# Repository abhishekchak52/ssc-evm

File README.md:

# ssc-evm
The Electronic Voting Machine for the St. Stephen's College Student's Union Society Elections for 2016-2017. With love from the Electronics Society

The basic design of the EVM is based on the Atmel ATmega328 chip which is at the heart of the Arduino UNO.
The final circuit will use only the chip instead of the entire Arduino board. The code is written in the Arduino language.

##TODO
* Make a working prototype using the Arduino UNO.
* Test for bugs.
* Port to a 40 AVR PDIP chip.

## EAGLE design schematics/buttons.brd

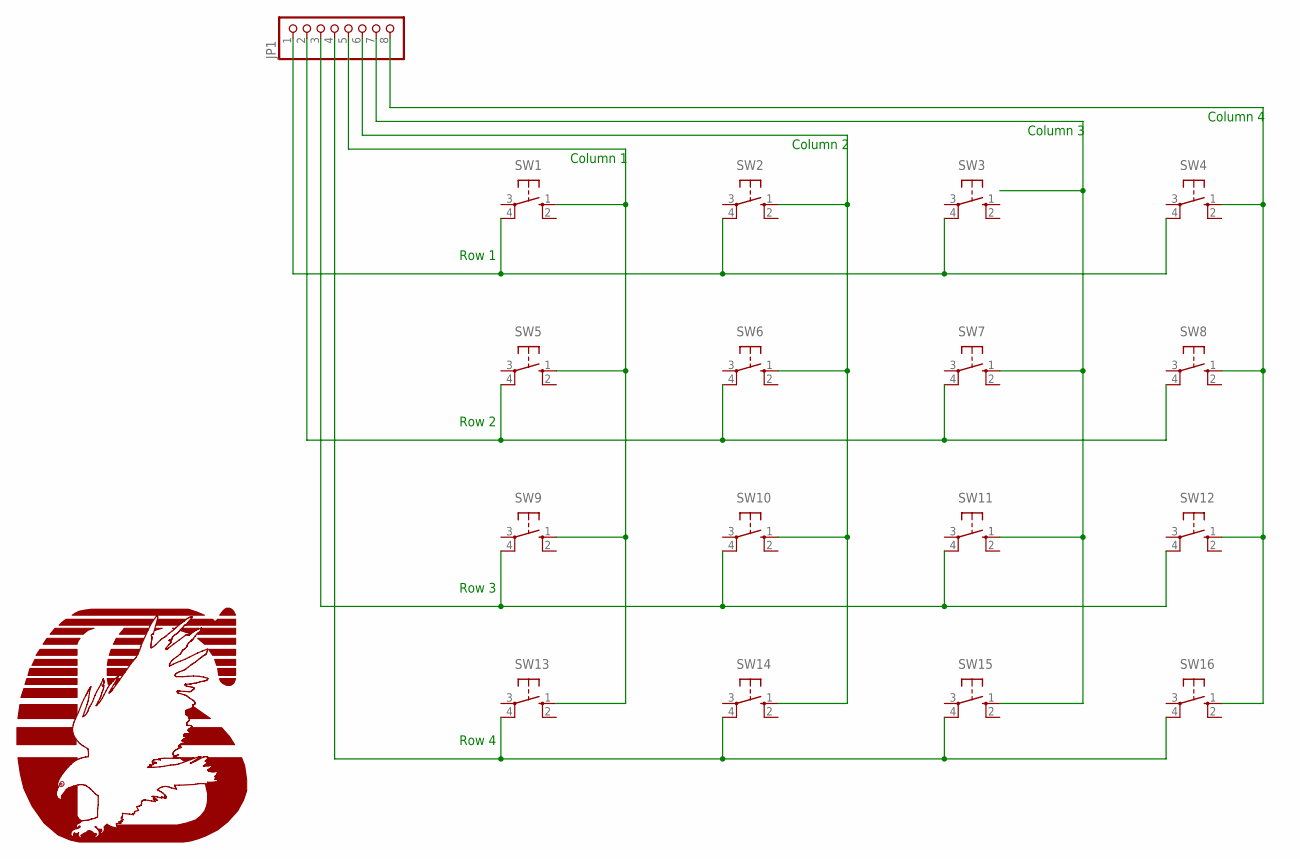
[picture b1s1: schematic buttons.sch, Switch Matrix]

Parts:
JP1: PINHD-1X8-3.5MM; 1X08-3.5MM
SW1, SW2, SW3, SW4, SW5, SW6, SW7, SW8, SW9, SW10, SW11, SW12, SW13, SW14, SW15, SW16: 10-XX; B3F-10XX

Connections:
unnamed: JP1.1, SW1.4 (P1), SW2.4 (P1), SW3.4 (P1), SW4.4 (P1)
unnamed: JP1.2, SW5.4 (P1), SW6.4 (P1), SW7.4 (P1), SW8.4 (P1)
unnamed: JP1.3, SW9.4 (P1), SW10.4 (P1), SW11.4 (P1), SW12.4 (P1)
unnamed: JP1.4, SW13.4 (P1), SW14.4 (P1), SW15.4 (P1), SW16.4 (P1)
unnamed: JP1.5, SW1.1 (S), SW5.1 (S), SW9.1 (S), SW13.1 (S)
unnamed: JP1.6, SW2.1 (S), SW6.1 (S), SW10.1 (S), SW14.1 (S)
unnamed: JP1.7, SW7.1 (S), SW11.1 (S), SW15.1 (S)
unnamed: JP1.8, SW4.1 (S), SW8.1 (S), SW12.1 (S), SW16.1 (S)

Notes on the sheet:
Row 1
Row 2
Row 3
Row 4
Column 1
Column 2
Column 3
Column 4

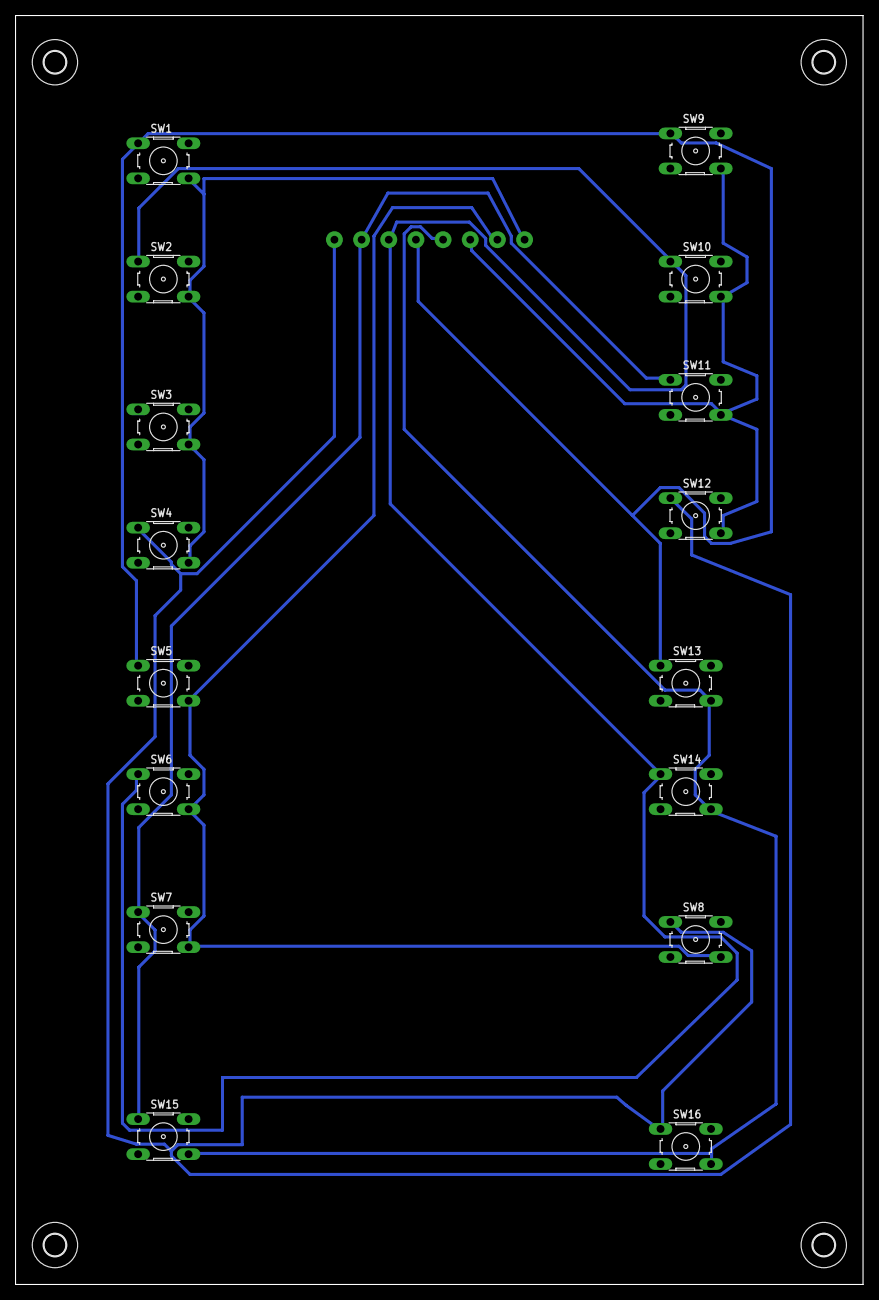
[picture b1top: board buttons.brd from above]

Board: 2 copper layers, 109.2 x 163.5 mm, 21 parts (1 on the bottom side), 8 nets.

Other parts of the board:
U$1, U$2, U$3, U$4: 2,8

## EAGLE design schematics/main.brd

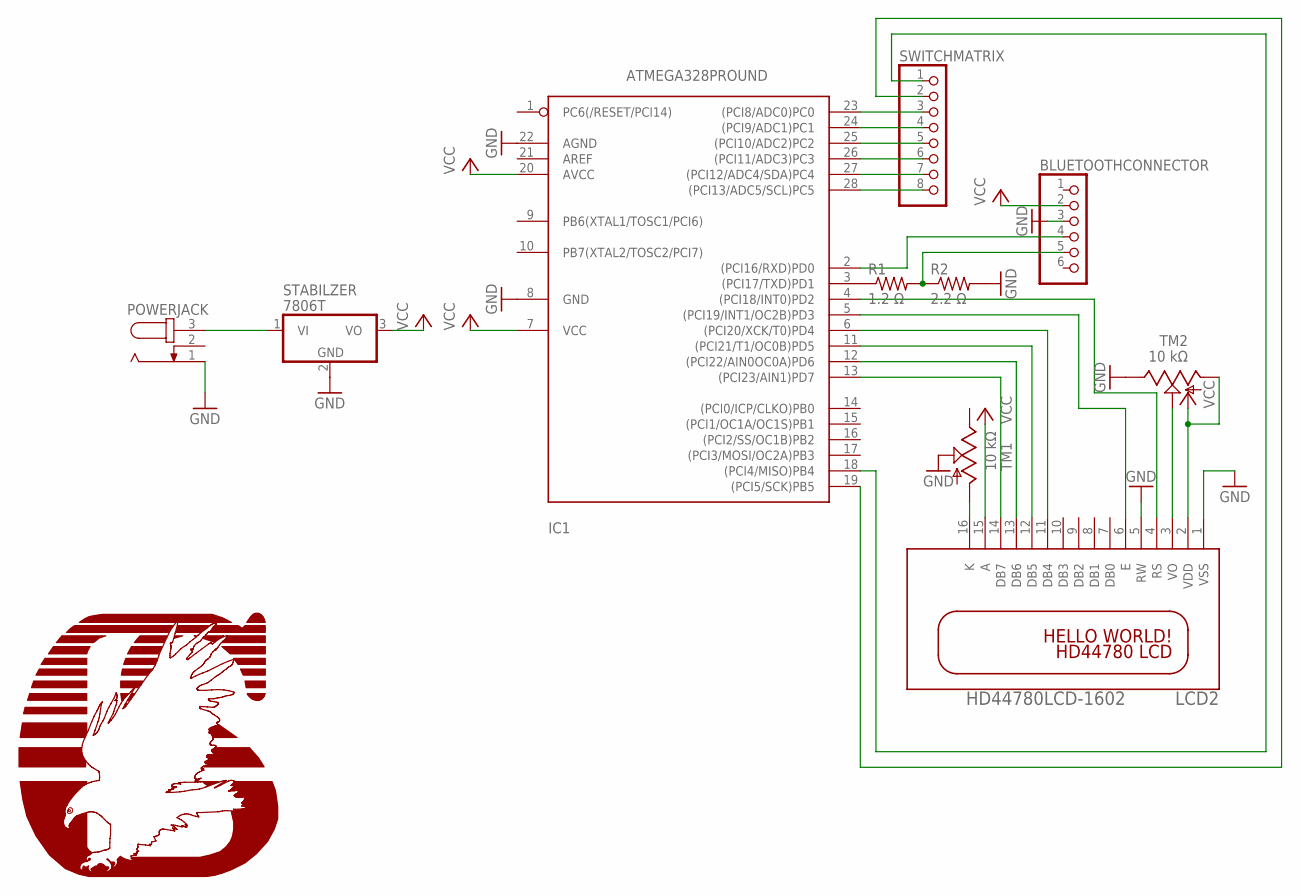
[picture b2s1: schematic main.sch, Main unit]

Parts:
BLUETOOTHCONNECTOR: PINHD-1X6B; 1X06-BIG
IC1: ATMEGA328PROUND; DIL28-3-ROUND
LCD2: HD44780LCD-1602; LCD1602
POWERJACK: JACK-PLUG0; SPC4077
R1: 1.2 Ω; 0207/10
R2: 2.2 Ω; 0207/10
STABILZER: 7806T; TO220H
SWITCHMATRIX: PINHD-1X8BIG; 1X08-BIG
TM1, TM2: 10 kΩ; 6MM

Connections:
GND: BLUETOOTHCONNECTOR.3, IC1.8 (GND), IC1.22 (AGND), LCD2.1 (VSS), LCD2.5 (RW), POWERJACK.1, R2.2, STABILZER.2 (GND), TM1.S, TM2.E
unnamed: BLUETOOTHCONNECTOR.4, IC1.2 ((PCI16/RXD)PD0)
unnamed: IC1.3 ((PCI17/TXD)PD1), R1.1
unnamed: BLUETOOTHCONNECTOR.5, R1.2, R2.1
unnamed: IC1.4 ((PCI18/INT0)PD2), LCD2.4 (RS)
unnamed: IC1.5 ((PCI19/INT1/OC2B)PD3), LCD2.6 (E)
unnamed: IC1.13 ((PCI23/AIN1)PD7), LCD2.14 (DB7)
unnamed: IC1.12 ((PCI22/AIN0OC0A)PD6), LCD2.13 (DB6)
unnamed: IC1.11 ((PCI21/T1/OC0B)PD5), LCD2.12 (DB5)
unnamed: LCD2.16 (K), TM1.A
unnamed: LCD2.3 (VO), TM2.S
unnamed: IC1.6 ((PCI20/XCK/T0)PD4), LCD2.11 (DB4)
unnamed: IC1.23 ((PCI8/ADC0)PC0), SWITCHMATRIX.3
unnamed: IC1.24 ((PCI9/ADC1)PC1), SWITCHMATRIX.4
unnamed: IC1.25 ((PCI10/ADC2)PC2), SWITCHMATRIX.5
unnamed: IC1.26 ((PCI11/ADC3)PC3), SWITCHMATRIX.6
unnamed: IC1.27 ((PCI12/ADC4/SDA)PC4), SWITCHMATRIX.7
unnamed: IC1.28 ((PCI13/ADC5/SCL)PC5), SWITCHMATRIX.8
unnamed: IC1.18 ((PCI4/MISO)PB4), SWITCHMATRIX.1
unnamed: IC1.19 ((PCI5/SCK)PB5), SWITCHMATRIX.2
unnamed: POWERJACK.3, STABILZER.1 (VI)
VCC: BLUETOOTHCONNECTOR.2, IC1.7 (VCC), IC1.20 (AVCC), LCD2.2 (VDD), LCD2.15 (A), STABILZER.3 (VO), TM2.A

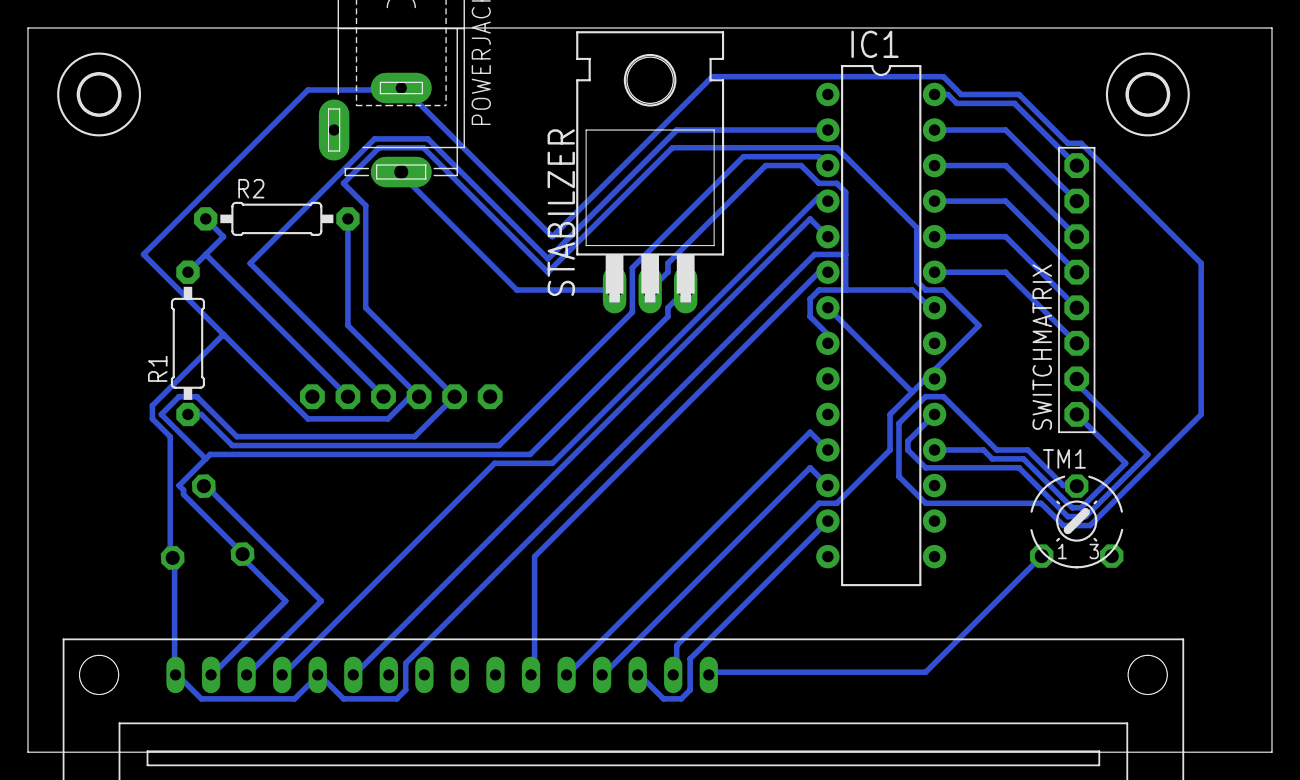
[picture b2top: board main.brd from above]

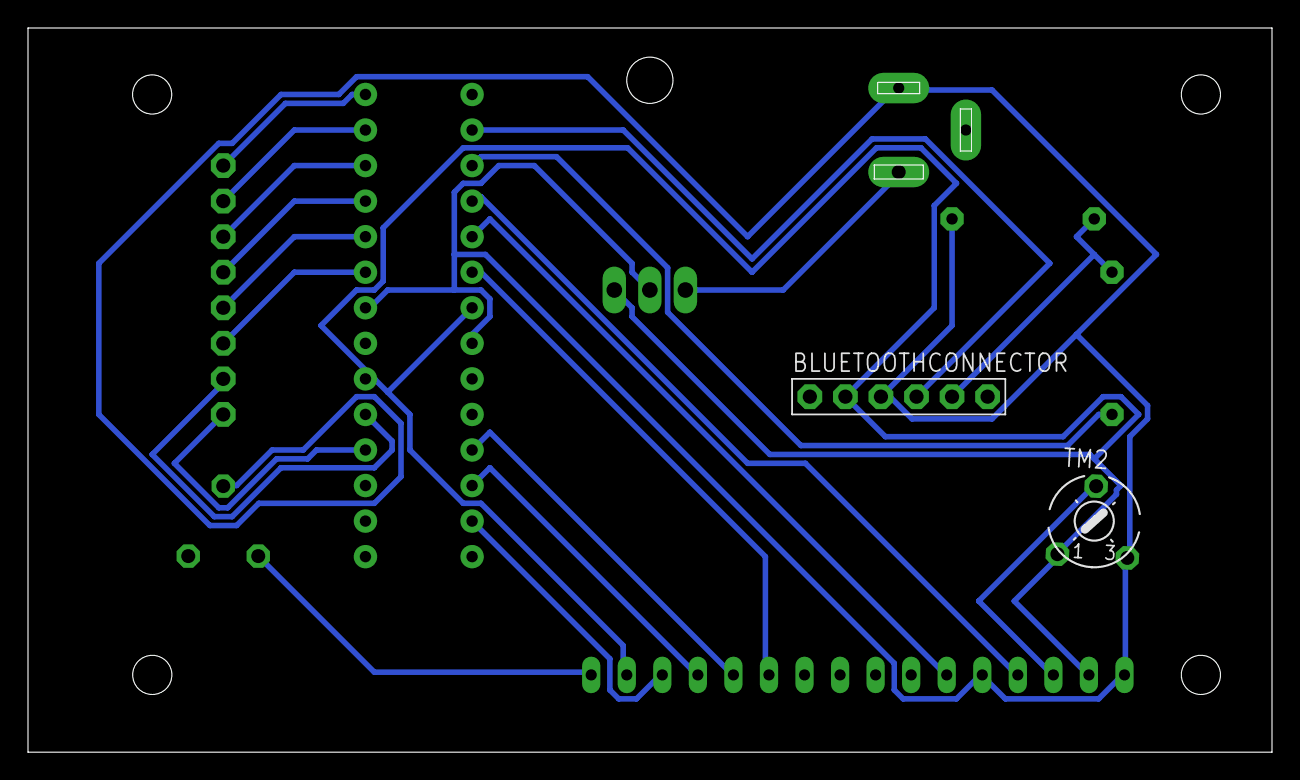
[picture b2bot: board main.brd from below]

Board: 2 copper layers, 88.9 x 51.7 mm, 12 parts (2 on the bottom side), 22 nets.

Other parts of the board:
U$1, U$2: 2,8

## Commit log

2016-05-29 Added TODO
2016-05-30 Nightly update 05302016
2016-06-03 Created the Arduino branch of the project. This branch is the main area of development until the problems with the MegaCore problems are sorted out.
2016-07-06 Wrote basic client and server programs. Added test program for faulty server.
2016-07-06 Tested server to client enabler.
2016-07-06 Configured for bidirectonal communication.
    Server sends enabled. Client sends back vote.
    Loop until user declines enable.
2016-07-06 Added cancel vote functionality on 'C' key
    Pressing the 'C' button cancels your current input and restarts the ballot.
2016-07-06 Set up server to wait for 4 bits to arrive and then read 4 bits
2016-07-06 Testing client to server communication.
2016-07-06 Server accepts only 4 bit strings. Client sends only 4 bit strings.
2016-07-06 Client 4bit configure
    Client echoes 4bit string to lcd, then writes to serial if string is 4
    bit
2016-07-12 Added Cadsoft Eagle schematics and PCB design files
    The main circuit and the buttons board each have two files: one .sch
    which is an eagle schematic and a .brd which is the PCB file
2016-08-05 Added ballot format and error handling
    Error handling for the voting process.
    The procedure for the ballot is also included
